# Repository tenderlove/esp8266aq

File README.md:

# My ESP8266 + Plantower AQ sensor project

This project is an ESP8266 combined with an AQ sensor and temp / humidity
sensor.  I have these set up around my house so I can monitor air quality and
temp.  The sensor publishes data to an MQTT server, then I have a listener that
connects to the MQTT server and writes all of the AQ data to an Influx
database.  I'm using Grafana to graph the data in the InfluxDB.

## Overview

Here is a photo of the completed project:

The sensor gets power over USB.  When you power the sensor up, it will create
an ad-hoc wifi network.  You can connect to that network then configure the
sensor with the network you want it to connect to.

## Hardware

The PCB is found in the [pcb](pcb) directory.  It's just a Kicad project.  The
[README](pcb/README.md) in that folder has more information about the hardware
side of this project (including parts, etc).

## Firmware

The firmware is found in the [firmware](firmware) directory.  The
[README](firmware/README.md) file in that folder has more information about the
firmware side of this project.

## Grafana

Here is a sample graph of the data:

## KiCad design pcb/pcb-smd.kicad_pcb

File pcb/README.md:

# My ESP8266 + Plantower AQ Sensor Project PCB

This is the PCB for the project.  I've checked in the gerber files in
`gerbers.zip`, so you can just upload that to a PCB manufacturer and get PCBs
made.  I like JLCPCB.

## Parts List

Here are the parts I used:

* [ESP-12F](https://www.digikey.com/en/products/detail/adafruit-industries-llc/2491/5761206) for WiFi [China](https://www.aliexpress.com/item/32339917567.html)
* [BME280](https://www.aliexpress.com/item/32862844557.html) for temp / humidity over I2C
* [PMS5003](https://www.aliexpress.com/item/32834164058.html) for Air Quality
* [MCP1700](https://www.digikey.com/en/products/detail/microchip-technology/MCP1700-3302E-TO/652680) 3.3v regulator
* 100nf capacitor (4.7mm ceramic disc)
* 47nf capacitor (4.7mm ceramic disc)
* 10uf capacitor (4mm radial)
* 2x 10k resistors (THT, 0207)
* 2x 5.1k resistors (THT, 0207)
* [WM7626CT-ND](https://www.digikey.com/product-detail/en/molex/0532610871/WM7626CT-ND/699113) Molex SMD connector for the AQ sensor [Europe](https://www.reichelt.nl/molex-pin-header-smd-picoblade-1x8-polig-stekker-molex-532610871-p186231.html)
* [USB4085-GF-A](https://www.digikey.com/en/products/detail/gct/USB4085-GF-A/9859733) for 5v power supply and serial communication
* [4 pin header](https://www.digikey.com/product-detail/en/sullins-connector-solutions/PPTC041LFBN-RC/S7002-ND/810144) to plug in the BME280 breakout board [Europe](https://www.reichelt.nl/female-header-2-54mm-straight-1x4-bkl-10120946-p266671.html)
* [MCP2221a](https://www.digikey.com/en/products/detail/microchip-technology/MCP2221A-I-P/6009296) for programming the ESP and serial communication
* [2x JST SH 4 pin Vertical Connector](https://www.adafruit.com/product/4328). These are optional, they're just for future extension to the board
* [IC Socket](https://www.digikey.com/en/products/detail/te-connectivity-amp-connectors/1-2199298-3/5022040) for mounting the MCP2221a

## Assembly

Some of these parts are surface mount parts and they can be somewhat tricky to solder.
I recommend using a [flux pen](https://www.amazon.com/gp/product/B074J6R1KQ/) and [fine solder wire](https://www.amazon.com/gp/product/B071G1J3W6/).

I recommend soldering in the following order:

* Resistors
* ESP
* Ceramic capacitors
* MCP1700 Voltage regulator
* IC Socket for MCP2221a
* 10uf radial capacitor
* Molex socket
* JST headers (if using)
* Header socket for BME breakout board
* USB connector

I soldered in that order because I found it easiest to keep the connectors
close to the PCB.

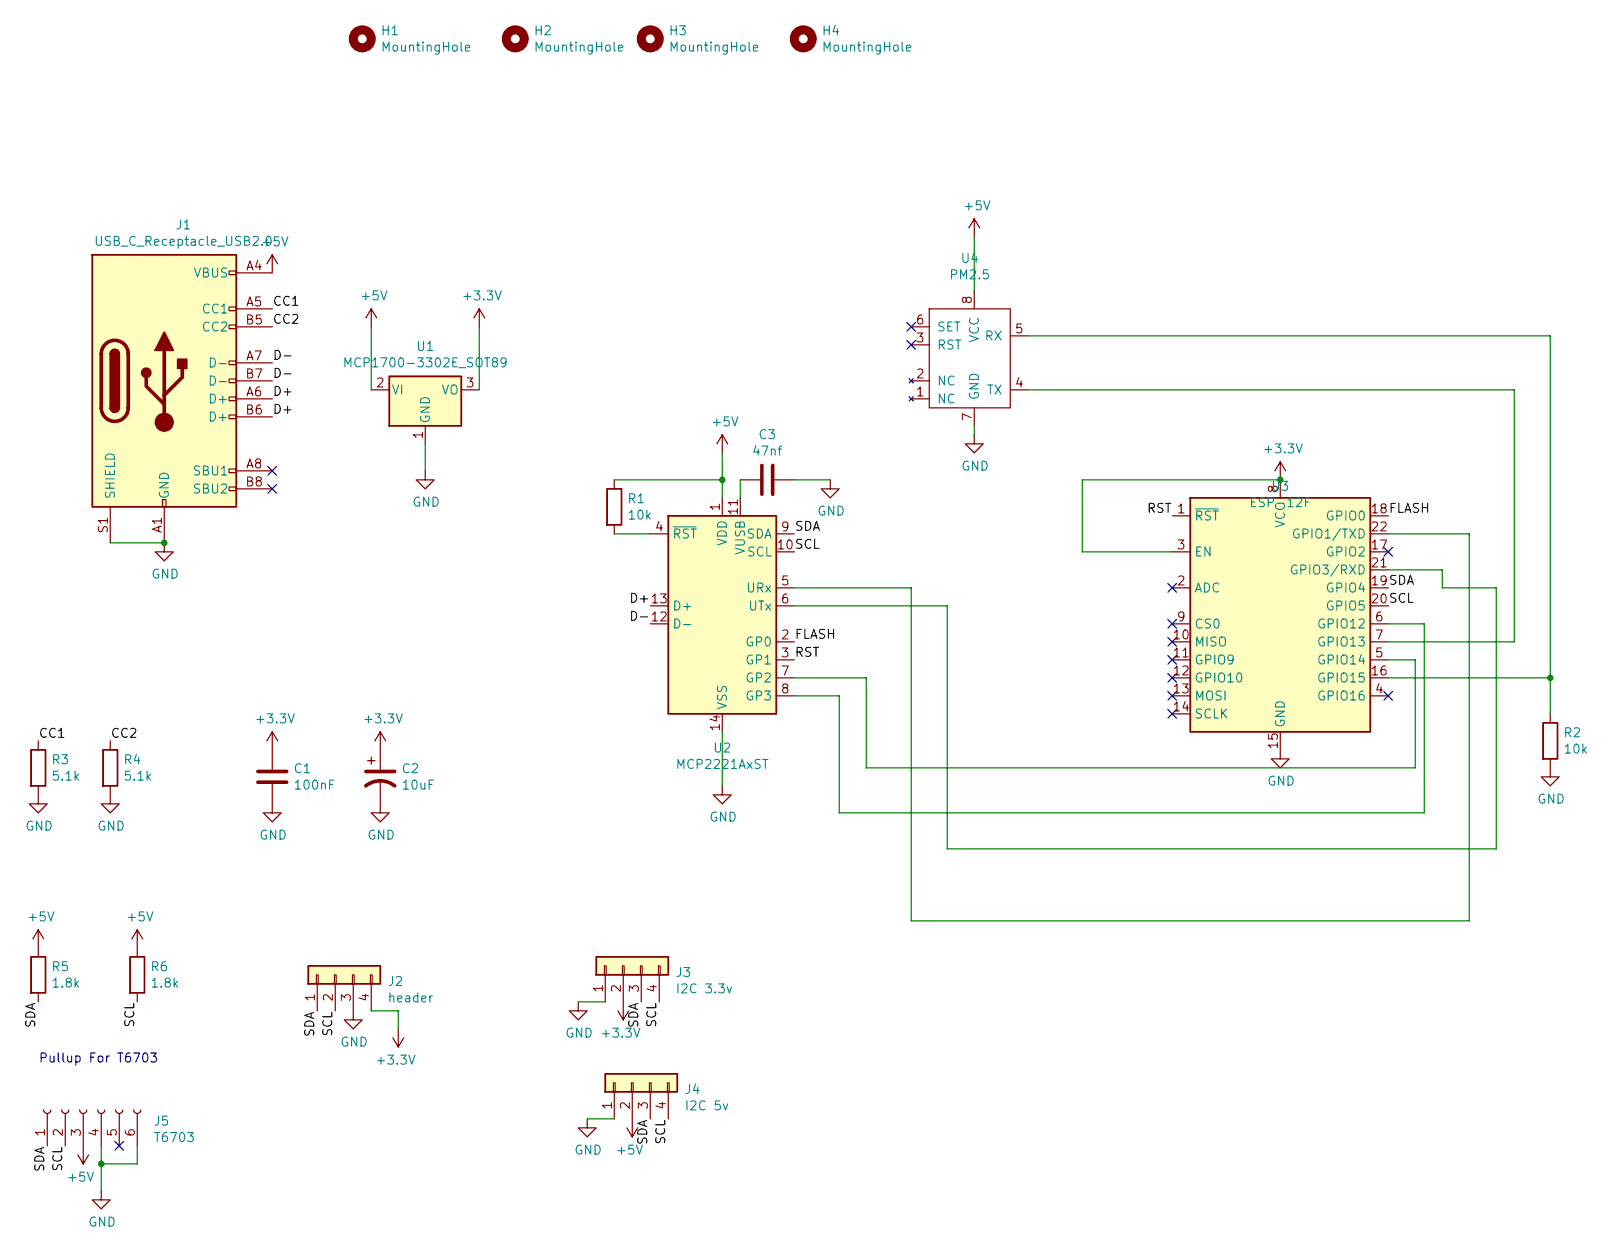
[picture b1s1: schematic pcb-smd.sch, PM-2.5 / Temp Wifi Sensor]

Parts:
C1: 100nF; C_1206_3216Metric_Pad1.42x1.75mm_HandSolder
C2: 10uF; C_1206_3216Metric_Pad1.42x1.75mm_HandSolder
C3: 47nf; C_1206_3216Metric_Pad1.42x1.75mm_HandSolder
H1, H2, H3, H4: MountingHole; MountingHole_2.5mm_Pad_Via
J1: USB_C_Receptacle_USB2.0; USB_C_Receptacle_GCT_USB4085
J2: header; PinSocket_1x04_P2.54mm_Vertical
J3: I2C 3.3v; JST_SH_BM04B-SRSS-TB_1x04-1MP_P1.00mm_Vertical
J4: I2C 5v; JST_SH_BM04B-SRSS-TB_1x04-1MP_P1.00mm_Vertical
J5: T6703; PinSocket_1x06_P2.54mm_Vertical
R1, R2: 10k; R_1206_3216Metric_Pad1.42x1.75mm_HandSolder
R3, R4: 5.1k; R_1206_3216Metric_Pad1.42x1.75mm_HandSolder
R5, R6: 1.8k; R_1206_3216Metric_Pad1.42x1.75mm_HandSolder
U1: MCP1700-3302E_SOT89; SOT-89-3
U2: MCP2221AxST; TSSOP-14_4.4x5mm_P0.65mm
U3: ESP-12F; ESP-12E
U4: PM2.5; Molex_PicoBlade_53261-0871_1x08-1MP_P1.25mm_Horizontal

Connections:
+3V3: C1.1, C2.1, J2.4, J3.2, U1.3 (VO), U3.3 (EN), U3.8 (VCC)
+5V: J1.A4 (VBUS), J1.A9 (VBUS), J1.B4 (VBUS), J1.B9 (VBUS), J4.2, J5.3, R1.1, R5.1, R6.1, U1.2 (VI), U2.1 (VDD), U4.8 (VCC)
/CC1: J1.A5 (CC1), R3.1
/CC2: J1.B5 (CC2), R4.1
/D+: J1.A6 (D+), J1.B6 (D+), U2.13 (D+)
/D-: J1.A7 (D-), J1.B7 (D-), U2.12 (D-)
/FLASH: U2.2 (GP0), U3.18 (GPIO0)
/RST: U2.3 (GP1), U3.1 (~RST)
/SCL: J2.2, J3.4, J4.4, J5.2, R6.2, U2.10 (SCL), U3.20 (GPIO5)
/SDA: J2.1, J3.3, J4.3, J5.1, R5.2, U2.9 (SDA), U3.19 (GPIO4)
GND: C1.2, C2.2, C3.1, J1.A1 (GND), J1.A12 (GND), J1.B1 (GND), J1.B12 (GND), J1.S1 (SHIELD), J2.3, J3.1, J4.1, J5.4, J5.6, R2.2, R3.2, R4.2, U1.1 (GND), U2.14 (VSS), U3.15 (GND), U4.7 (GND)
unnamed: C3.2, U2.11 (VUSB)
unnamed: R1.2, U2.4 (~RST)
unnamed: R2.1, U3.16 (GPIO15), U4.5 (RX)
unnamed: U2.5 (URx), U3.22 (GPIO1/TXD)
unnamed: U2.6 (UTx), U3.21 (GPIO3/RXD)
unnamed: U2.7 (GP2), U3.5 (GPIO14)
unnamed: U2.8 (GP3), U3.6 (GPIO12)
unnamed: U3.7 (GPIO13), U4.4 (TX)

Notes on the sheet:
Pullup For T6703

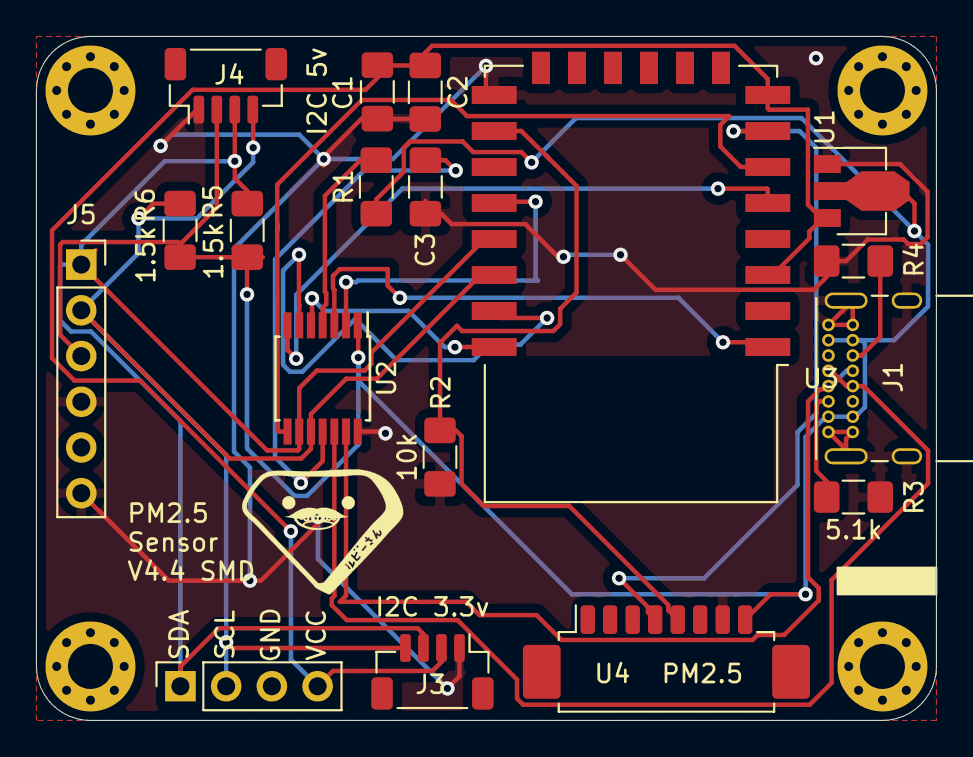
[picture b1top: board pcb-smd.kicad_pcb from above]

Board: 2 copper layers, 50.0 x 38.0 mm, 22 parts (0 on the bottom side), 19 nets.

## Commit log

2019-09-03 Create LICENSE
2020-04-22 Don't hardcode the wifi access point
2020-04-22 update the client
2020-04-22 add readme
2020-04-22 adding temp / humidity sensor
2020-04-22 adding makefile to build stuff
2020-04-22 adding gitignore
2020-04-22 adding pcb
2020-04-22 adding esp8266 footprint submodule
2020-04-22 fix the sample program
2020-04-22 updating documentation
2020-04-22 updating docs
2020-04-22 fix typo
2020-04-22 make the PCB the same size as the plantower sensor
2020-04-22 be more specific in parts
2020-04-22 Fix directories, add a clean task
2020-04-23 Add link to the client
2020-04-23 Add another link
2020-05-10 Combine temperature and humidity reading
    This also sends a more precise humidity reading
2020-05-10 Don't depend on external libraries
2020-05-10 Add PubSubClient
2020-05-10 Use my serial port
2020-05-11 Convert to MQTT
2020-05-17 Format
2020-05-17 Don't publish when not connected
2020-05-17 Different serial port
2020-05-17 Report temperature separately from AQ
2020-05-17 Reset if input[0] doesn't match
    I believe this fixes an issue where the communication with the AQ sensor
    gets out of sync and we stay off by one skipping over the magic start
    sequence.
2020-05-17 Reset index if inputString[0] doesn't match
    I believe this fixes an issue where the communication with the AQ sensor
    gets out of sync and we stay off by one skipping over the magic start
    sequence.
2020-05-18 Drop bytes from serial when more than two packets
2020-06-11 Added reichelt for parts
2020-06-11 add a version to the protocol
2020-06-11 s/6 pin/8 pin/
    This should have been an 8 pin connector. Fixes #4
2020-10-06 Detect usbserial
2020-10-06 Add basic web server
2020-10-18 More firmware into src
2020-10-18 Setup platformio
2020-10-18 serve files from FS
2020-10-18 Working status.json
2020-10-18 Basic working status page
2020-10-18 Enable ArduinoOTA
2020-10-18 Use separate server for status via URL fragment
2020-10-18 Improve page styling
2020-10-18 Remove arduino
2020-10-18 Avoid infinite loop in mqtt_reconnect
    Instead, just try to reconnect once
2020-10-19 Working read from config
2020-10-19 Add some esp8266 debugging info
2020-10-22 Move pms5003 into class
2021-01-25 refactor programming script
2021-02-04 somewhat case
2021-02-05 it seems not bad now
2021-02-05 updating pcb
2021-02-05 fixing file name
2021-02-05 adding makefile and stls
2021-02-05 updating makefile and scad
2021-02-05 updating case, removing unused stuff
2021-02-05 clean up firmware a little
2021-02-05 adding a client
2021-02-05 updating readme
2021-02-05 adding dependencies
2021-02-05 adding a serial client
2021-02-06 updating model again
2021-02-06 refactoring
2021-02-06 this is not used anymore
2021-02-06 removing unused libraries
2021-02-09 adding lid to container with some test text
2021-02-09 add some text to the cable case lol
2021-02-12 fix bugs introduced by my bad merge
2021-02-12 just read from the serial port for now
2021-02-14 Use build flags to specify default MQTT settings.
    I want to specify the connection information as environment variables so
    I don't have to check them in. Now I can do this:
    ```
    $ MQTT_SERVER=10.0.1.211 make flash && ruby utils/serial-client.rb
    ```
2021-02-14 Update firmware to use compile options for configuration
2021-02-14 send temp / rh every second
2021-02-14 fix serial echo of temp / rh
2021-02-14 Cache calculated topic name, avoid varg
    push publish to measurement object
2021-02-14 gp2 and 3 should be low by default
2021-02-15 update firmware readme
2021-02-15 calculate dewpoint
2021-02-15 Add client script for sensors
2021-02-15 Poll less agressively
2021-02-15 Add support for mqtt username and password
2021-02-15 Longer wait between mqtt retries
2021-02-15 Fix port suggestion
2021-02-17 Turn on the LED when we've connected to the MQTT server
2021-02-17 I guess Kicad wanted to change some stuff
2021-02-17 Fix OpenSCAD binary location
    It seems like homebrew no longer installs `openscad`, so this points to
    the binary in the /Applications folder
2021-02-17 make the text stick out
2021-02-17 add new STL files
2021-02-17 renaming directory
2021-02-17 remove unused file
2021-02-17 update the hardware readme
2021-02-17 Add assembly documentation
2021-02-17 broadcast node name on mdns
    So you can access `node-name.local` via browser
2021-02-27 fix uplaodfs target
2021-02-27 Fix name
2021-02-28 making it look better
2021-02-28 use GP2 on the MCP2221a to control serial output
2021-03-04 Fix floating point recording
2021-03-04 Move measurement classes in to their own files
2021-03-11 update pcb with pulldown resistors for USB-C
2021-03-14 oops. Fix gp3 pin
2021-03-23 updating firmware
2021-03-23 updating gerbers
2021-03-23 updating case
2021-04-18 add tp6703 support
2021-04-18 add smd gerbers and pcb
2021-04-18 update mqtt to influx client
2021-04-18 add readme for case
2021-05-16 updating
2021-05-16 update photos
2021-05-16 Update license to include PCB artwork
2021-05-16 fix readme
2021-07-11 lets use the right method!
2023-01-06 ensure fan vent is properly subtracted
    Previously, the fan vent subtraction was leaving a thin layer on the
    wall, but we want a hole.
    I _think_ it might have something to do with [this](https://en.wikibooks.org/wiki/OpenSCAD_User_Manual/The_OpenSCAD_Language#difference) section of the docs, namely:
    > It is mandatory that surfaces that are to be removed by a difference
    > operation have an overlap, and that the negative piece being removed
    > extends fully outside of the volume it is removing that surface from.
2025-11-06 Bump mqtt from 0.5.0 to 0.7.0 in /firmware
    Bumps [mqtt](https://github.com/njh/ruby-mqtt) from 0.5.0 to 0.7.0.
    - [Release notes](https://github.com/njh/ruby-mqtt/releases)
    - [Changelog](https://github.com/njh/ruby-mqtt/blob/main/NEWS.md)
    - [Commits](https://github.com/njh/ruby-mqtt/compare/v0.5.0...v0.7.0)
    ---
    updated-dependencies:

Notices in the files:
pcb/pcb-smd.kicad_pcb:
License: CC BY 4.0
pcb/pcb-smd.sch:
creativecommons.org/licenses/by/4.0
